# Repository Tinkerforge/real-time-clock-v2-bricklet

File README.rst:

Real-Time Clock Bricklet 2.0
============================

This repository contains the firmware source code and the hardware design
files. The documentation generator configs can be found at
https://github.com/Tinkerforge/generators

Repository Content
------------------

software/:
 * examples/: Examples for all supported languages
 * build/: Compiled files
 * src/: Source code of firmware
 * Makefile: Makefile to build project

hardware/:
 * Contains KiCad project files and additionally schematics as PDF

datasheets/:
 * Contains datasheets for sensors and complex ICs that are used

Hardware
--------

The hardware is designed with the open source EDA Suite KiCad
(http://www.kicad.org). Before you are able to open the files,
you have to install the Tinkerforge kicad-libraries
(https://github.com/Tinkerforge/kicad-libraries). You can either clone
them directly in hardware/ or clone them in a separate folder and
symlink them into hardware/
(ln -s kicad_path/kicad-libraries project_path/hardware). After that you
can open the .pro file in hardware/ with KiCad and from there view and
modify the schematics and the PCB layout.

Software
--------

If you want to do your own Brick/Bricklet firmware development we highly
recommend that you use our build environment setup script and read the
tutorial (https://www.tinkerforge.com/en/doc/Tutorials/Tutorial_Build_Environment/Tutorial.html).

To compile the C code we recommend you to install the newest GNU Arm Embedded
Toolchain (https://launchpad.net/gcc-arm-embedded/+download).
You also need to install bricklib2 (https://github.com/Tinkerforge/bricklib2).

You can either clone it directly in software/src/ or clone it in a
separate folder and symlink it into software/src/
(ln -s bricklib_path/bricklib2 project_path/software/src/). Finally make sure to
have CMake installed (http://www.cmake.org/cmake/resources/software.html).

After that you can build the firmware by invoking make in software/.
The firmware (.zbin) can then be found in software/build/ and uploaded
with brickv (click button "Flashing" on start screen).

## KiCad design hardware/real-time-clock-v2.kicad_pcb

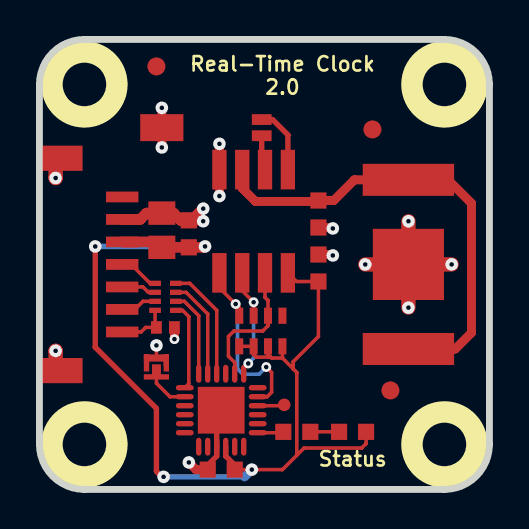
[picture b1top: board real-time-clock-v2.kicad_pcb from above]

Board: 2 copper layers, 25.0 x 25.0 mm, 26 parts (0 on the bottom side), 20 nets.

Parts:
BT1: BATTERY; BATTERY_HOLDER_2998
C1: 220pF; C0402F
C2: 10uF; C0805E
C3, C4, C5, C6: 100nF; C0603F
D1: blue; D0603F
Fiducial_Mark: VAL**; Fiducial_Mark
Fiducial_Mark#2, Fiducial_Mark#3: VAL**; Fiducial_Mark
P1: CON-SENSOR; CON-SENSOR2
P2: Debug; DEBUG_PAD
P3: Boot; SolderJumper
R1: 1k; R0603F
RP1: 82; 4X0402
RP2: 2k2; 4X0603
U1: XMC1100; QFN24-4x4mm-0.5mm
U2: PCF85263AT; SO-8
U3, U4, U5, U6: DRILL; DRILL_NP
VAL: CE_5mm
VAL#2: WEEE_7mm_back; WEEE_7mm
X1: 32.768kHz; AB26TRQ

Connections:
3V3: C2.1, C3.1, C4.1, C5.1, D1.1, P1.3, RP2.5, RP2.6, RP2.7, RP2.8, U1.10, U2.8
GND: BT1.2, C1.2, C2.2, C3.2, C4.2, C5.2, C6.2, P1.2, P1.EP, P3.1, U1.9, U1.EXP, U2.4, X1.3
INT: RP2.3, U1.20, U2.7
unnamed: BT1.1, C6.1, U2.3
unnamed: C1.1, P1.7, RP1.4
unnamed: D1.2, R1.2
unnamed: P1.4, RP1.1
unnamed: P1.5, RP1.2
unnamed: P1.6, RP1.3
unnamed: P2.1, U1.16
unnamed: P3.2, U1.2
unnamed: R1.1, U1.13
unnamed: U2.1, X1.2
unnamed: U2.2, X1.1
S-CLK: RP1.7, U1.23
S-CS: RP1.8, U1.22
S-MISO: RP1.5, U1.1
S-MOSI: RP1.6, U1.24
SCL: RP2.2, U1.19, U2.6
SDA: RP2.1, U1.17, U2.5

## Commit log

2018-01-15 add new hardware prototype
2018-02-20 Add .gitignore
2018-02-20 Cleanup KiCad libraries config
    Ensure LibDir=kicad-libraries and LibName1=tinkerforge.
    Remove special library.
2018-03-01 Add skeleton firmware
2018-03-02 Add datasheets
2018-03-02 Switch to XMC1302 for more flash
2018-03-02 Add firmware
2018-03-05 Remove unused flash-size define
2018-03-14 Don't setup callback header if not necessary
2018-03-15 fix ce logo orientation
2018-03-16 fix weee logo
2018-03-27 specify processor
2018-04-16 Add 3d information (final)
2018-04-16 Add 3d model (*.FCStd & .*step)
2018-05-04 Rename files
2018-05-04 Add schematic PDF
2018-05-28 Add examples
2018-05-29 Use XMC11 instread of XMC13
2018-05-29 Use max 512 byte for EEPROM emulation
2018-05-29 Remove unnecessary "set to false initialization" directly after memset to 0
2018-05-29 Disable debug
2018-05-29 Compile with Os to be sure that the firmware fits into the 16kb MCU
2018-06-04 Also cache alarm configuration if setting interval-only alarm
    Otherwise, the alarm will not be triggerred.
2018-06-04 In case of an timeout we only reset the i2c fifo and pcf85263a. If we reset everything (including zeroing the pcf85263a struct, the timeout can not be handled properly (i2c reset code is not executed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
2018-06-07 Update changelog for initial release
2018-06-18 Change capacitor footprint(s) to C0402F 78634
2018-06-28 Fix readme
2018-07-11 Add Makefile with docker support
2018-07-11 Remove obsolete generate_makefile scripts
2018-07-11 Update directory structure and build instructions
2018-08-07 Read date-time before setting alarm
    Instead of relying on the cached date-time being up-to-date. Because
    the logic will be removed that keeped the cached date-time up-to-date.
2018-08-07 Remove unnecessary I2C communication to avoid date-time jumps
    Instead of reading the date-time registers all the time, only read
    them on request.
2018-08-07 Do not reset alarm state varaibles on I2C error
2018-08-08 Add commit ref
2018-08-16 Make date-time/timestamp getters synchronous again to avoid potential timeouts
    Update date-time every 250ms, interpolate with micorcontroller clock in between.
2018-09-14 vbnet: Fix typo in comment
2018-10-04 Increase version for new release (changes in bricklib2)
2018-10-04 Add rev to changelog
2018-11-06 Add rust examples
2018-11-07 rust: Accept host names for ip connection, fix naming inconsistencies
2018-11-07 rust: Rename callback receivers.
2018-12-14 Add go examples.
2018-12-18 go: Change import path.
2018-12-18 go: Change import path again.
2018-12-20 Fix constant handling in examples.
2018-12-20 rust: Reformat examples.
2019-01-24 mqtt: Add examples.
2019-01-24 mqtt: Fix example header.
2019-01-24 mqtt: Remove executable bit in example permissions.
2019-01-24 go: Minor example fixes.
2019-01-24 mqtt: Minor example fixes.
2019-03-28 mqtt: Fix whitespace.
2019-05-29 Activate memory optimized irq handler
    The Real-Time Clock Bricklet 2.0 has very little flash left. Since
    it does not use any IRQs itself, it can use the memory optimized
    version of the new bootloader SPI IRQ implementation without any
    drawbacks. Otherwise we would run out of flash here.
2019-06-03 Fix typo in define
2019-08-22 c: Adapt to bindings changes
2020-01-13 examples: Use python3 input instead of python2 raw_input.
2020-01-13 examples: mqtt: Remove trailing whitespace.
2020-08-19 Add uc examples.
2020-08-25 uc: Fix whitespace
2020-08-27 uc: Use %lld to print 64 bit integers.
2020-08-27 uc: Fix warnings.
2020-08-31 uc: Use fixed-with placeholders in format strings.
2020-09-02 uc: Add example driver note.
2021-10-25 Update KiCad link
    https://www.kicad.org/blog/2021/10/Avoid-links-to-former-kicad-domain/
2022-04-19 examples: uc: Rename TF_HalContext to TF_HAL.
2022-04-27 uc: Adapt to bindings changes
2022-05-10 go: Fix format string
2022-07-06 Add license files.
2022-11-15 Fix race condition between set/get_date_time
    We had to move some code arround to save some flash to fix this bug...
2022-11-15 Add ref for v2.0.4
2025-10-04 Fix compatibility with new Docker build image (GCC 14.2.1)

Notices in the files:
hardware/real-time-clock-v2.kicad_pcb:
Licensed under CERN OHL v.1.1
Copyright (©) 2018, B.Nordmeyer
Copyright Tinkerforge GmbH 2018.
This documentation describes Open Hardware and is licensed under the
CERN OHL v. 1.1.
